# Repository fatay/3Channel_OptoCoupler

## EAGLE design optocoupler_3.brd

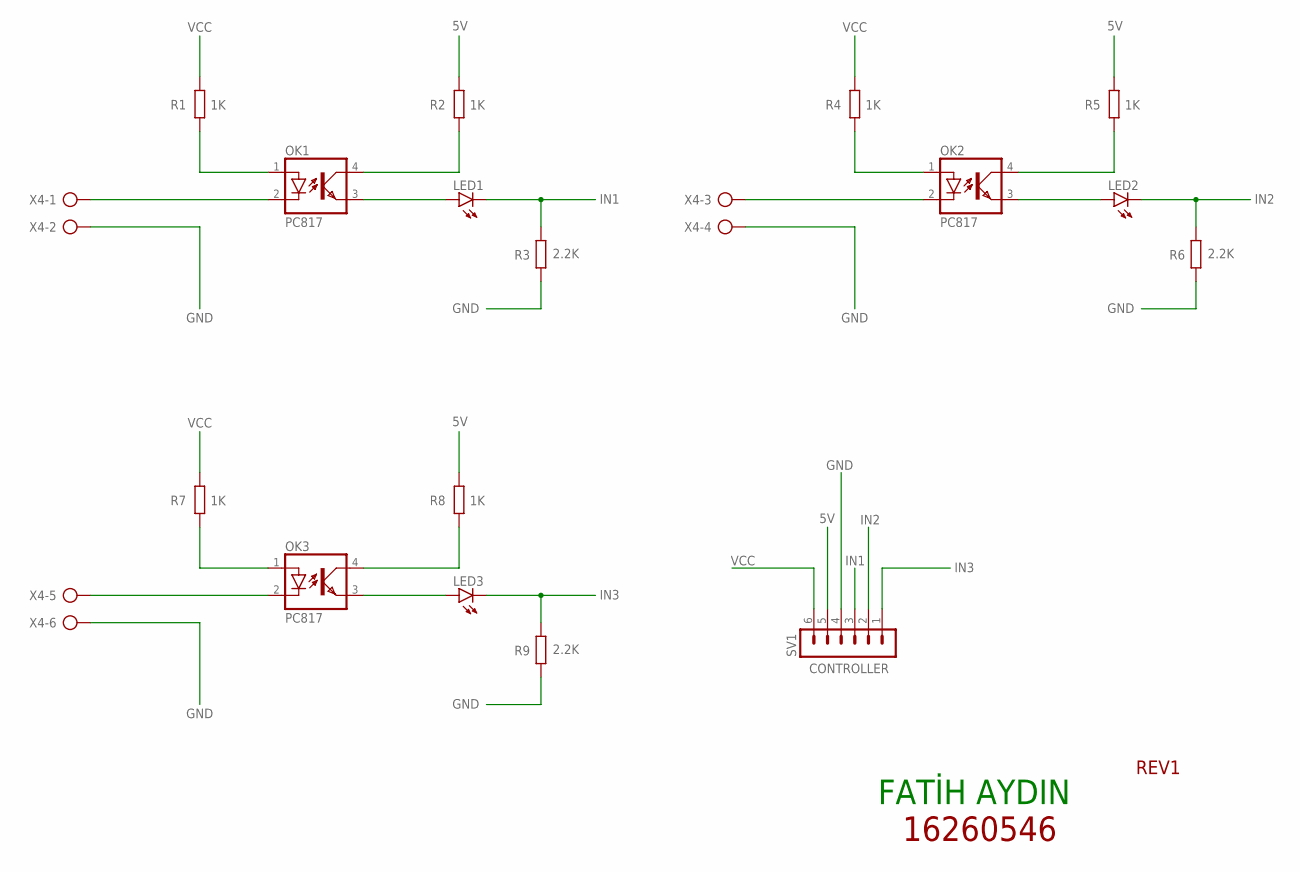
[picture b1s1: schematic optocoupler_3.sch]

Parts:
LED1, LED2, LED3: LED5MM
OK1, OK2, OK3: PC817; DIL04
R1, R2, R4, R5, R7, R8: 1K; 0204/7
R3, R6, R9: 2.2K; 0204/7
SV1: CONTROLLER; MA06-1
X4: AK300/6

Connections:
5V: R2.2, R5.2, R8.2, SV1.5
GND: R3.1, R6.1, R9.1, SV1.4, X4.2, X4.4, X4.6
IN1: LED1.K (C), R3.2, SV1.3
IN2: LED2.K (C), R6.2, SV1.2
IN3: LED3.K (C), R9.2, SV1.1
unnamed: OK1.1 (A), R1.1
unnamed: OK1.4 (COL), R2.1
unnamed: OK2.1 (A), R4.1
unnamed: OK2.4 (COL), R5.1
unnamed: OK1.2 (C), X4.1
unnamed: OK2.2 (C), X4.3
unnamed: LED1.A, OK1.3 (EMIT)
unnamed: LED2.A, OK2.3 (EMIT)
unnamed: OK3.1 (A), R7.1
unnamed: OK3.4 (COL), R8.1
unnamed: OK3.2 (C), X4.5
unnamed: LED3.A, OK3.3 (EMIT)
VCC: R1.2, R4.2, R7.2, SV1.6

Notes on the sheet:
FATİH AYDIN
16260546
REV1

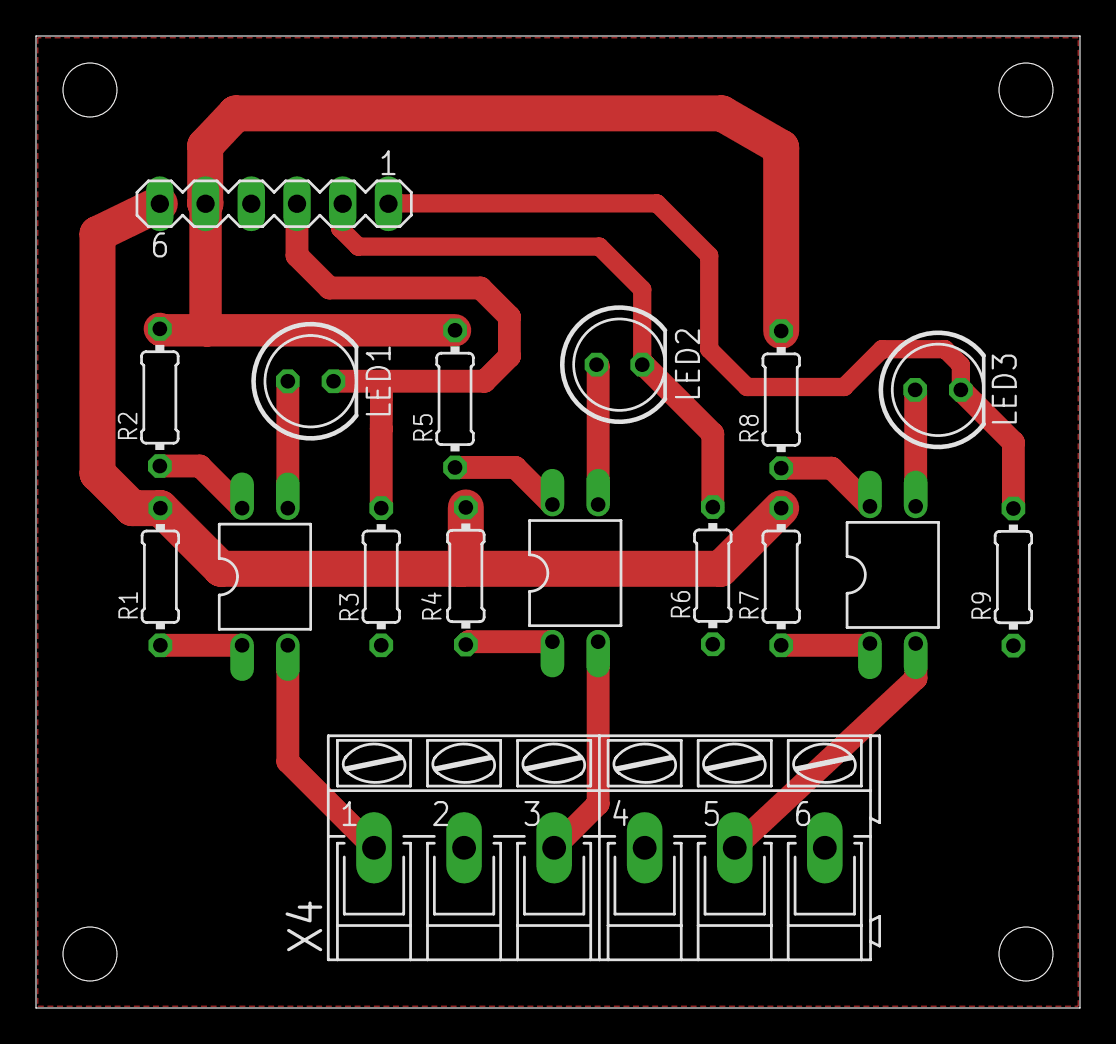
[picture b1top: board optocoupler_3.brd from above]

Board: 2 copper layers, 58.0 x 54.0 mm, 17 parts (0 on the bottom side), 18 nets.

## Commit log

2020-05-22 r1
    r1
